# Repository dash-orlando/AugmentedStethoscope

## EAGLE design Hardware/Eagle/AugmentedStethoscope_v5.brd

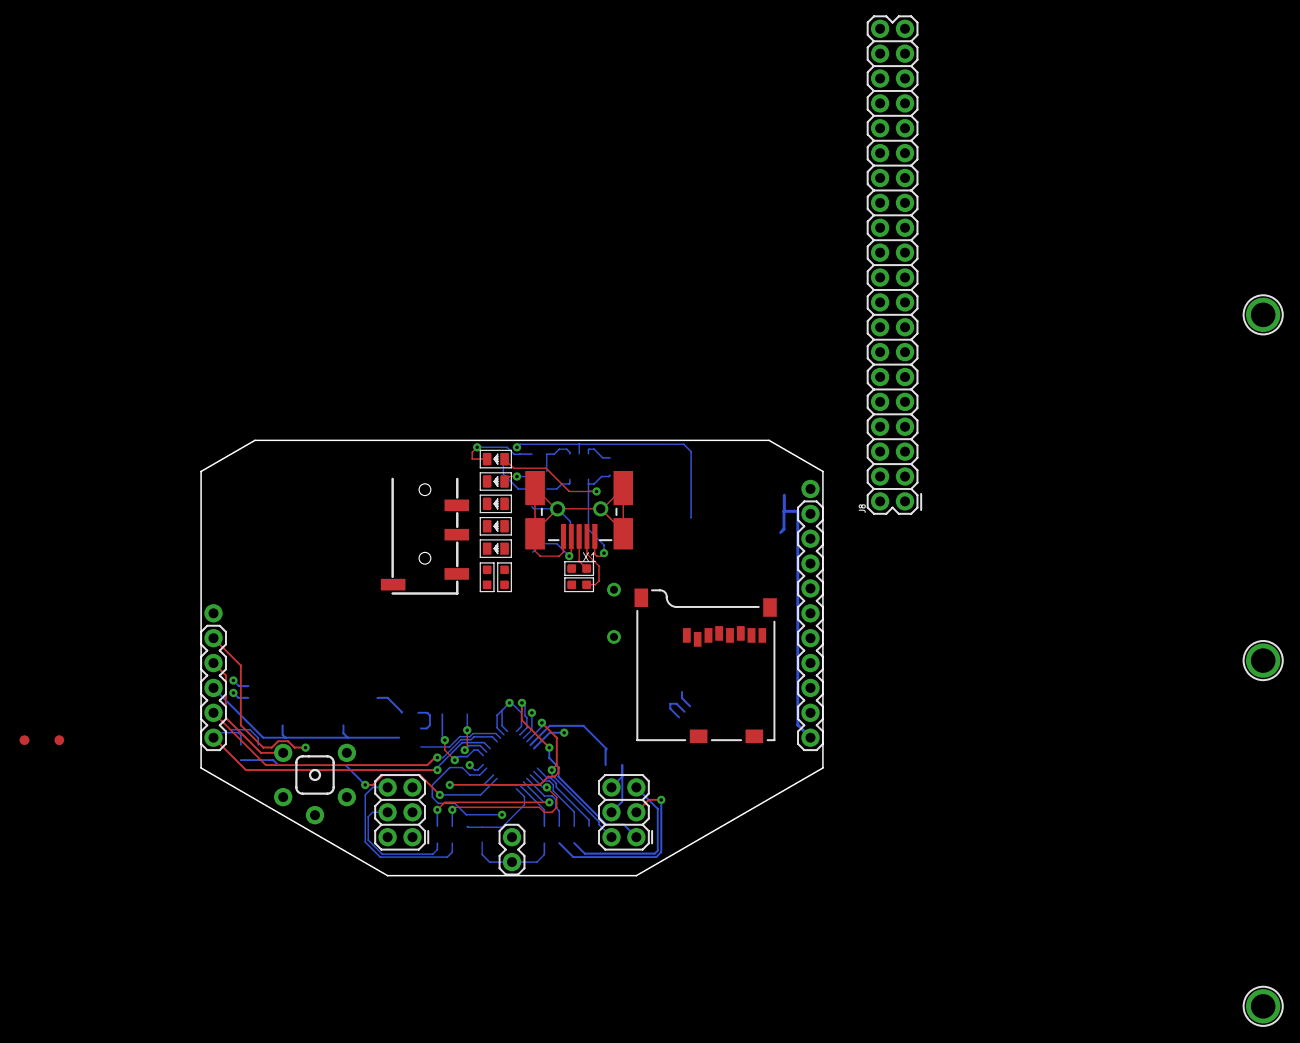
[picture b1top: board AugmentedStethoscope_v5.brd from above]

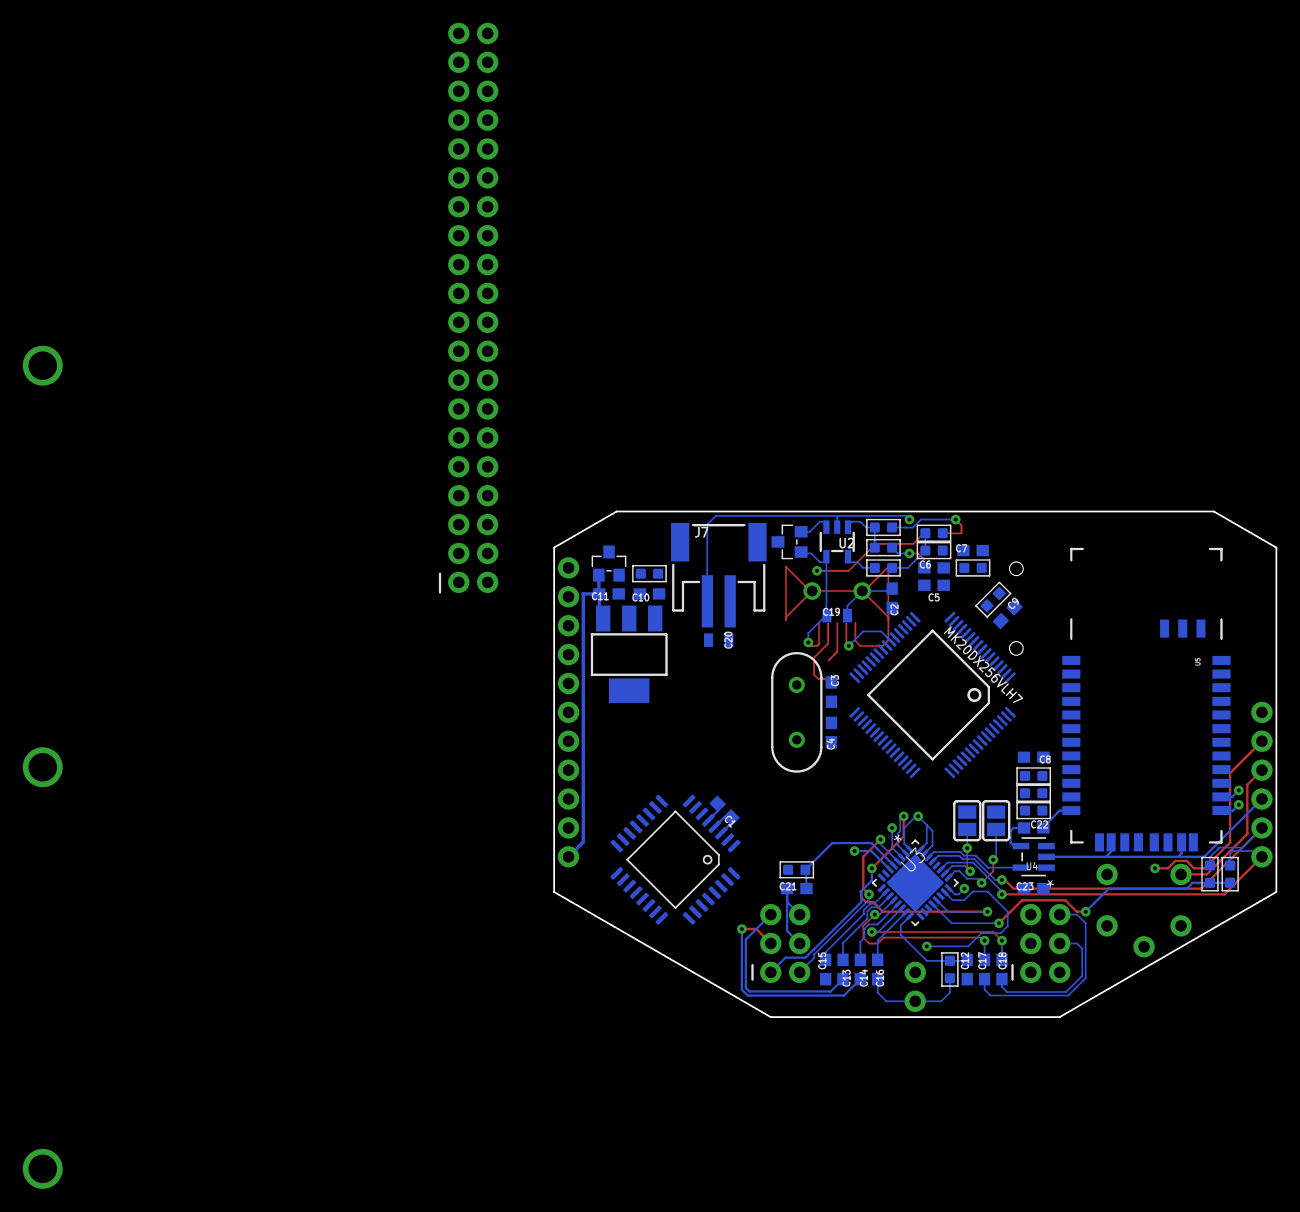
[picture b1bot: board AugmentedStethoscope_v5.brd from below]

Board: 2 copper layers, 63.5 x 44.5 mm, 77 parts (52 on the bottom side), 71 nets.

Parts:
C1, C2, C5, C6, C8, C9, C10, C16: 0.1uF; 0603
C3, C4: 22pF; 0603
C7, C11, C12, C13, C14, C17, C18, C21, C22, C23: 2.2uF; 0603
C15: 0.15uF; 0603
C19, C20: 10uF; 0805
FID1, FID2: FIDUCIAL""; FIDUCIAL_1MM
G1: 16MHz; HC49US
J1: 1X05
J2, J3: FEMALE 2x3; 2X3
J4: 1X10
J5: 1X02
J6: AUDIO_JACK_TRRSSMD_RA; AUDIO_JACK_3.5MM_TRRS_SMD_RA
J7: JSTPH; JSTPH2
J8: CONN_20X2; 2X20
JP1, JP2: M01SMDNS; 1X01NS
K1: MKL04Z32VLC4; LQFP32-08
K2: MK20DX256VLH7; LQFP64-05
P1, P2, P3: BLUE; LED-0805
P4: GREEN; LED-0805
P5: RED; LED-0805
R1, R2, R3, R11, R15, R17: 470; R0603
R4, R6, R9, R14, R19, R21: 10K; R0603
R5, R18: SOT-23
R7, R8: 33; R0603
R10, R12, R20: L0603
R13, R16: 2.2K; R0603
S1: ALPS_SKHH
SJ1, SJ2: SOLDERJUMPER
T1: MCP1825S; SOT-223
U1: microSD; MICRO-SD-SOCKET-PP
U2: MCP73831T-2ACI/OT; SOT23-5
U3: SGTL5000XNAA3R2; QFN32
U4: TPS79318DBVR; DBV5
U5: BLUETOOTH-RN41; RN41
U$1, U$3, U$15: MOUNTINGHOLE2.5; MOUNTINGHOLE_2.5_PLATED
X1: MINI-USB; MOLEX_SD-67503-010

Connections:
0/RX1: K2.39, R6.1
1/TX1: K2.40, R9.1
3.3V: C1.1, C8.1, C9.1, C11.1, J4.1, K1.3, K1.4, K2.3, K2.7, K2.30, K2.48, R5.1, R12.2, R14.2, R19.2, R20.2, R21.2, T1.3, U1.4, U3.20, U5.11
7/SPI_MOSI: J4.4, K2.59, U1.3
9: K2.46, U3.24
10/SPI_CS: K2.49, R14.1, U1.2
11: K2.51, U3.21
12/SPI_MISO: J4.5, K2.52, U1.7
13/LED: K2.50, P1.+, SJ2.2
14/SPI_SCK: J4.6, K2.58, U1.5
15/A1: J4.7, K2.43
18/A4/SDA: J1.1, K2.38, R19.1, U3.27
19/A5/SCL: J1.2, K2.37, R21.1, U3.29
20/A6/SPI_CS: J4.3, K2.62
21/A7/SPI_CS: J4.2, K2.63
22/A8: K2.44, SJ1.2
23/A9: K2.45, U3.23
AGND: C5.2, C6.2, C7.2, J4.8, K2.15, K2.16, R10.2
D3: P2.-, R2.2
D4: P3.-, R3.2
D+: R7.1, X1.3
D-: R8.1, X1.2
GND: C1.2, C2.2, C3.2, C4.2, C8.2, C9.2, C10.2, C11.2, C12.2, C15.1, C19.1, C20.1, C21.2, C22.2, C23.1, J1.3, J2.3, J2.5, J3.4, J3.6, J4.9, J5.1, J7.1, K1.5, K1.6, K2.4, K2.31, K2.47, P4.-, R1.1, R2.1, R3.1, R4.1, R10.1, R16.1, S1.3, S1.4, T1.2, T1.PAD, U1.6, U1.GND1, U1.GND2, U2.2, U3.1, U3.3, U3.7, U3.31, U3.32, U4.2, U5.1, U5.12, U5.25, U5.27, U5.28, U5.29, X1.5, X1.P$1, X1.P$2, X1.P$3, X1.P$4, X1.P$5, X1.P$6
HPGND: J2.1, J3.2, J6.EARTH, U3.4
HPL: J2.2, J6.TIP, U3.6
HPR: J3.1, J6.RING1, U3.2
ID: K1.10, K2.23, X1.4
LIL: C18.2, J2.4
LIL_ISO: C18.1, U3.14
LIR: C14.2, J3.3
LIR_ISO: C14.1, U3.13
LOL: C17.2, J2.6
LOL_ISO: C17.1, U3.12
LOR: C13.2, J3.5
LOR_ISO: C13.1, U3.11
MIC: C16.1, J5.2, R13.1
MIC_BIAS: C12.1, R13.2, U3.16
unnamed: C20.2, J7.2, R18.2, U2.3
unnamed: K1.16, K2.22
unnamed: K1.17, K2.24
unnamed: C15.2, U3.10
unnamed: C3.1, G1.1, K2.32
unnamed: C4.1, G1.2, K2.33
unnamed: C5.1, K2.14, R11.2
unnamed: C22.1, U4.4
unnamed: SJ1.1, U3.26
unnamed: K2.5, R7.2
unnamed: C6.1, K2.17
unnamed: C23.2, U3.30, U4.5
unnamed: SJ2.1, U3.25
unnamed: K2.6, R8.2
unnamed: C16.2, U3.15
unnamed: P3.+, U5.19
unnamed: C7.1, K2.13, R11.1, R12.1
unnamed: P1.-, R1.2
unnamed: C2.1, K2.21, R5.3
unnamed: K1.15, K2.25
unnamed: P5.-, R17.1
unnamed: R15.2, R17.2, U2.1
unnamed: P2.+, U5.21
unnamed: R16.2, U2.5
unnamed: P4.+, R15.1
unnamed: C21.1, R20.1, U3.5
PIO4: JP1.1, R4.2, U5.22
PROG: J1.4, K1.18, S1.1, S1.2
RESET: J1.5, K1.8, K1.25, K2.34
SMIRF_RX: R9.2, U5.13
SMIRF_TX: R6.2, U5.14
VIN: C10.1, J4.10, R18.3, T1.1, U4.1, U4.3
VRTC: JP2.1, R5.2
V_USB: C19.2, P5.+, R18.1, U2.4, X1.1

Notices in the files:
parts and their libraries:
microbuilder: This work is placed in the public domain, and may be freely used for commercial and non-commercial work with the following conditions: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
SparkFun-Connectors: Licensing: Creative Commons ShareAlike 4.0 International - https://creativecommons.org/licenses/by-sa/4.0
